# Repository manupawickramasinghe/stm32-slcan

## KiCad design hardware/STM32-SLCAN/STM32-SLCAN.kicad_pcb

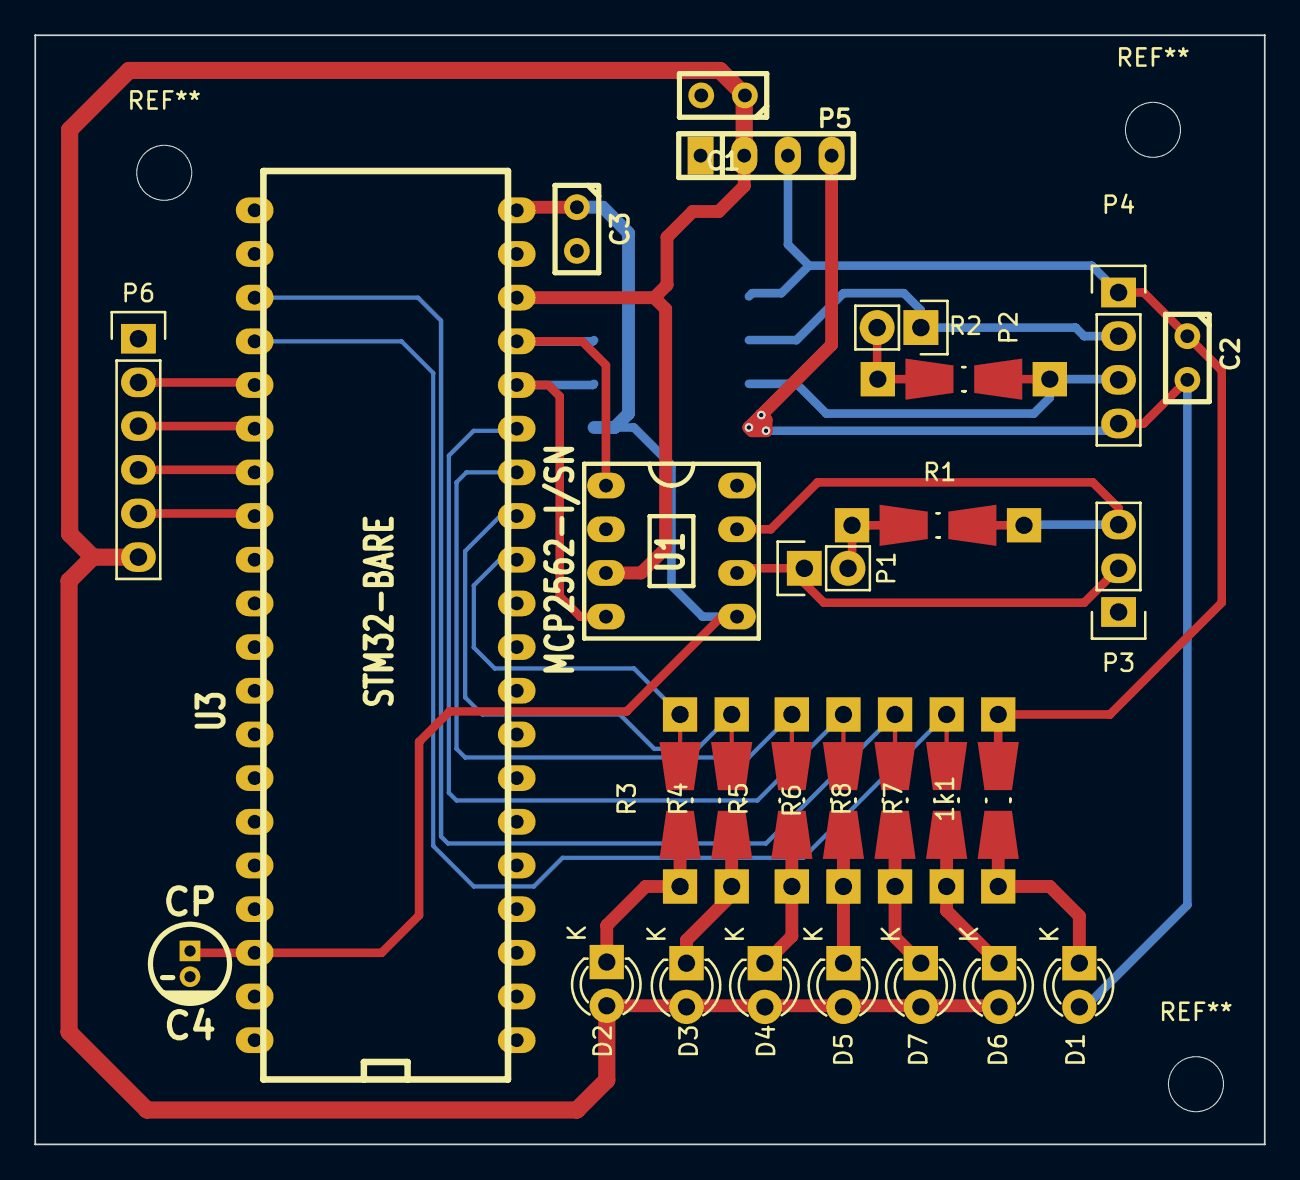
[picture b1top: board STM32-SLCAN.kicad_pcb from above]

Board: 2 copper layers, 71.5 x 64.5 mm, 29 parts (1 on the bottom side), 30 nets.

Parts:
1k1: R; Resistor_SMD+THTuniversal_0805to1206_RM10_HandSoldering_Rev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
C1, C2, C3: C; cnp_3mm_disc
C4: CP; CP_4x5mm
D1, D2, D3, D4, D5, D6, D7: LED; LED-3MM
P1, P2: Term; Pin_Header_Straight_1x02
P3: CONN_01X03; Pin_Header_Straight_1x03
P4: CONN_01X04; Pin_Header_Straight_1x04
P5: CONN_01X04; r-sil_4
P6: CONN_01X06; Pin_Header_Straight_1x06
R1, R2: 120; Resistor_SMD+THTuniversal_0805to1206_RM10_HandSoldering_Rev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
R3, R4, R5, R6, R7, R8: 1k5; Resistor_SMD+THTuniversal_0805to1206_RM10_HandSoldering_Rev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
U1: MCP2562-I/SN; dil_8-300_socket
U2: ISO1050; mdip_8
U3: STM32-BARE; dil_40-600

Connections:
+3V3: C3.1, C4.1, U1.5, U2.1, U3.20, U3.38
+5V: C1.1, D2.2, D3.2, D4.2, D5.2, D6.2, D7.2, P5.2, P6.6, U1.3, U3.18
+5VA: C2.2, D1.2, P4.4, P5.4, U2.8
/CAN_OVF: R6.2, U3.15
/CAN_RX: R4.2, U3.13
/CAN_TX: R3.2, U3.12
/CTS: P6.2, U3.25
/RTS: P6.5, U3.28
/RxD: P6.3, U3.26
/RxD_LED: R8.2, U3.23
/TxD: P6.4, U3.27
/TxD_LED: R7.2, U3.24
/UART_OVF: R5.2, U3.14
GND: C1.2, C3.2, C4.2, P3.1, P5.1, P6.1, U1.2, U1.8, U2.4, U3.19, U3.39, U3.40
GNDA: 1k1.2, C2.1, P4.1, P5.3, U2.5
unnamed: 1k1.1, D1.1
unnamed: D2.1, R3.1
unnamed: D3.1, R4.1
unnamed: D4.1, R5.1
unnamed: D5.1, R6.1
unnamed: D6.1, R7.1
unnamed: D7.1, R8.1
unnamed: P1.1, P3.2, U1.6
unnamed: P1.2, R1.1
unnamed: P2.1, P4.2, U2.6
unnamed: P2.2, R2.1
unnamed: P3.3, R1.2, U1.7
unnamed: P4.3, R2.2, U2.7
unnamed: U1.1, U2.3, U3.17
unnamed: U1.4, U2.2, U3.16

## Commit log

2025-03-29 PCB Complete
